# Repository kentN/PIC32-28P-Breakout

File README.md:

# PIC32-28P-Breakout
Breakout board for PIC32 SSOP28 packages

## Features ##
- Two External Clock Option (EXTAL, SOSC)
- ICSP port (PGx3) for PIC32MM, PIC32MX1XX Series
- PIN19: user selectable, RC9(PIC32MM) or VSS (Soldering Jumper for PIC32MX) 
- Size: 33x15.2mm

## Support MCUs ##
- ◎ PIC32MMXXXXGPL028
- 〇 PIC32MX1XX
- △ PIC32MX2XX (ICSP PGC,PGD not work)

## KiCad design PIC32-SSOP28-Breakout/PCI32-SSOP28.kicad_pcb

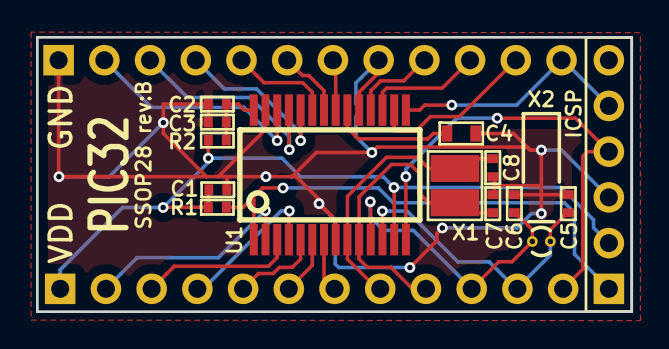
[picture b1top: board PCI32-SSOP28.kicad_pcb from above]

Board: 2 copper layers, 33.0 x 15.2 mm, 17 parts (1 on the bottom side), 27 nets.

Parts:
C1, C2: 0.1u; 0402
C3: 0.01u; 0402
C4: 10u; 0603
C5, C6, C7, C8: 30p; 0402
CN1, CN2: CONN_12; 1x12P_s
ICSP: CONN_6; 1x6P
J1: JMP; JUMPER
R1: 10k; 0402
R2: 4.7; 0402
U1: PIC32MMXXXXGPL028; SOIC28
X1: NX3225-8M; 3225-2
X2: 32.768k; Cylinder_6mm

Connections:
+3.3V: C1.1, CN1.1, ICSP.2, R1.2, R2.2, U1.13
/AVDD: C2.1, C3.1, R2.1, U1.28
GND: C1.2, C2.2, C3.2, C4.2, C5.2, C6.2, C7.2, C8.2, CN2.1, ICSP.3, J1.2, U1.8, U1.27
MCLR: ICSP.1, R1.1, U1.1
unnamed: C4.1, U1.20
unnamed: C5.1, CN1.11, U1.12, X2.1
unnamed: C6.1, CN1.10, U1.11, X2.2
unnamed: C7.1, CN1.9, U1.10, X1.1
unnamed: C8.1, CN1.8, U1.9, X1.2
unnamed: CN1.2, U1.2
unnamed: CN1.3, U1.3
unnamed: CN1.4, U1.4
unnamed: CN1.5, U1.5
unnamed: CN1.6, U1.6
unnamed: CN1.7, U1.7
unnamed: CN2.2, U1.26
unnamed: CN2.3, U1.25
unnamed: CN2.4, U1.24
unnamed: CN2.5, U1.23
unnamed: CN2.6, U1.22
unnamed: CN2.7, U1.21
unnamed: CN2.8, J1.1, U1.19
unnamed: CN2.9, U1.18
unnamed: CN2.10, U1.17
unnamed: CN2.11, U1.16
PGEC: CN2.12, ICSP.5, U1.15
PGED: CN1.12, ICSP.4, U1.14

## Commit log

2017-05-19 fix filenames
2017-09-20 fix silk typo
